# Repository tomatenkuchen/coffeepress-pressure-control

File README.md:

# La Pavoni Europiccola with embedded electronic pressure control
Pavoni Espresso Makers in their oldtimer form come with limited and inefficient steam pressure control (litterally steam all you can, and vent the surplus away). 
A power control via TRIAC and electronic pressure sensor can make a significant difference on power intake and startup time.

Attention! This design involves dealing with high voltages that can be dealy of lead to serious injury. Only qualified personel is allowed to assemble, test and use these schematics. There's no warranity or responsibility from my side, if things go wrong.
## documentation
all documentation is found in form of an [mdbook](https://rust-lang.github.io/mdBook/index.html).

## hardware
as this project is esp32 based, we need a pcb to mount the chip, the sensors and the power stage. the pcb design and component simulation was made with kicad 8.

## software
software is planned to be a rust embedded project.

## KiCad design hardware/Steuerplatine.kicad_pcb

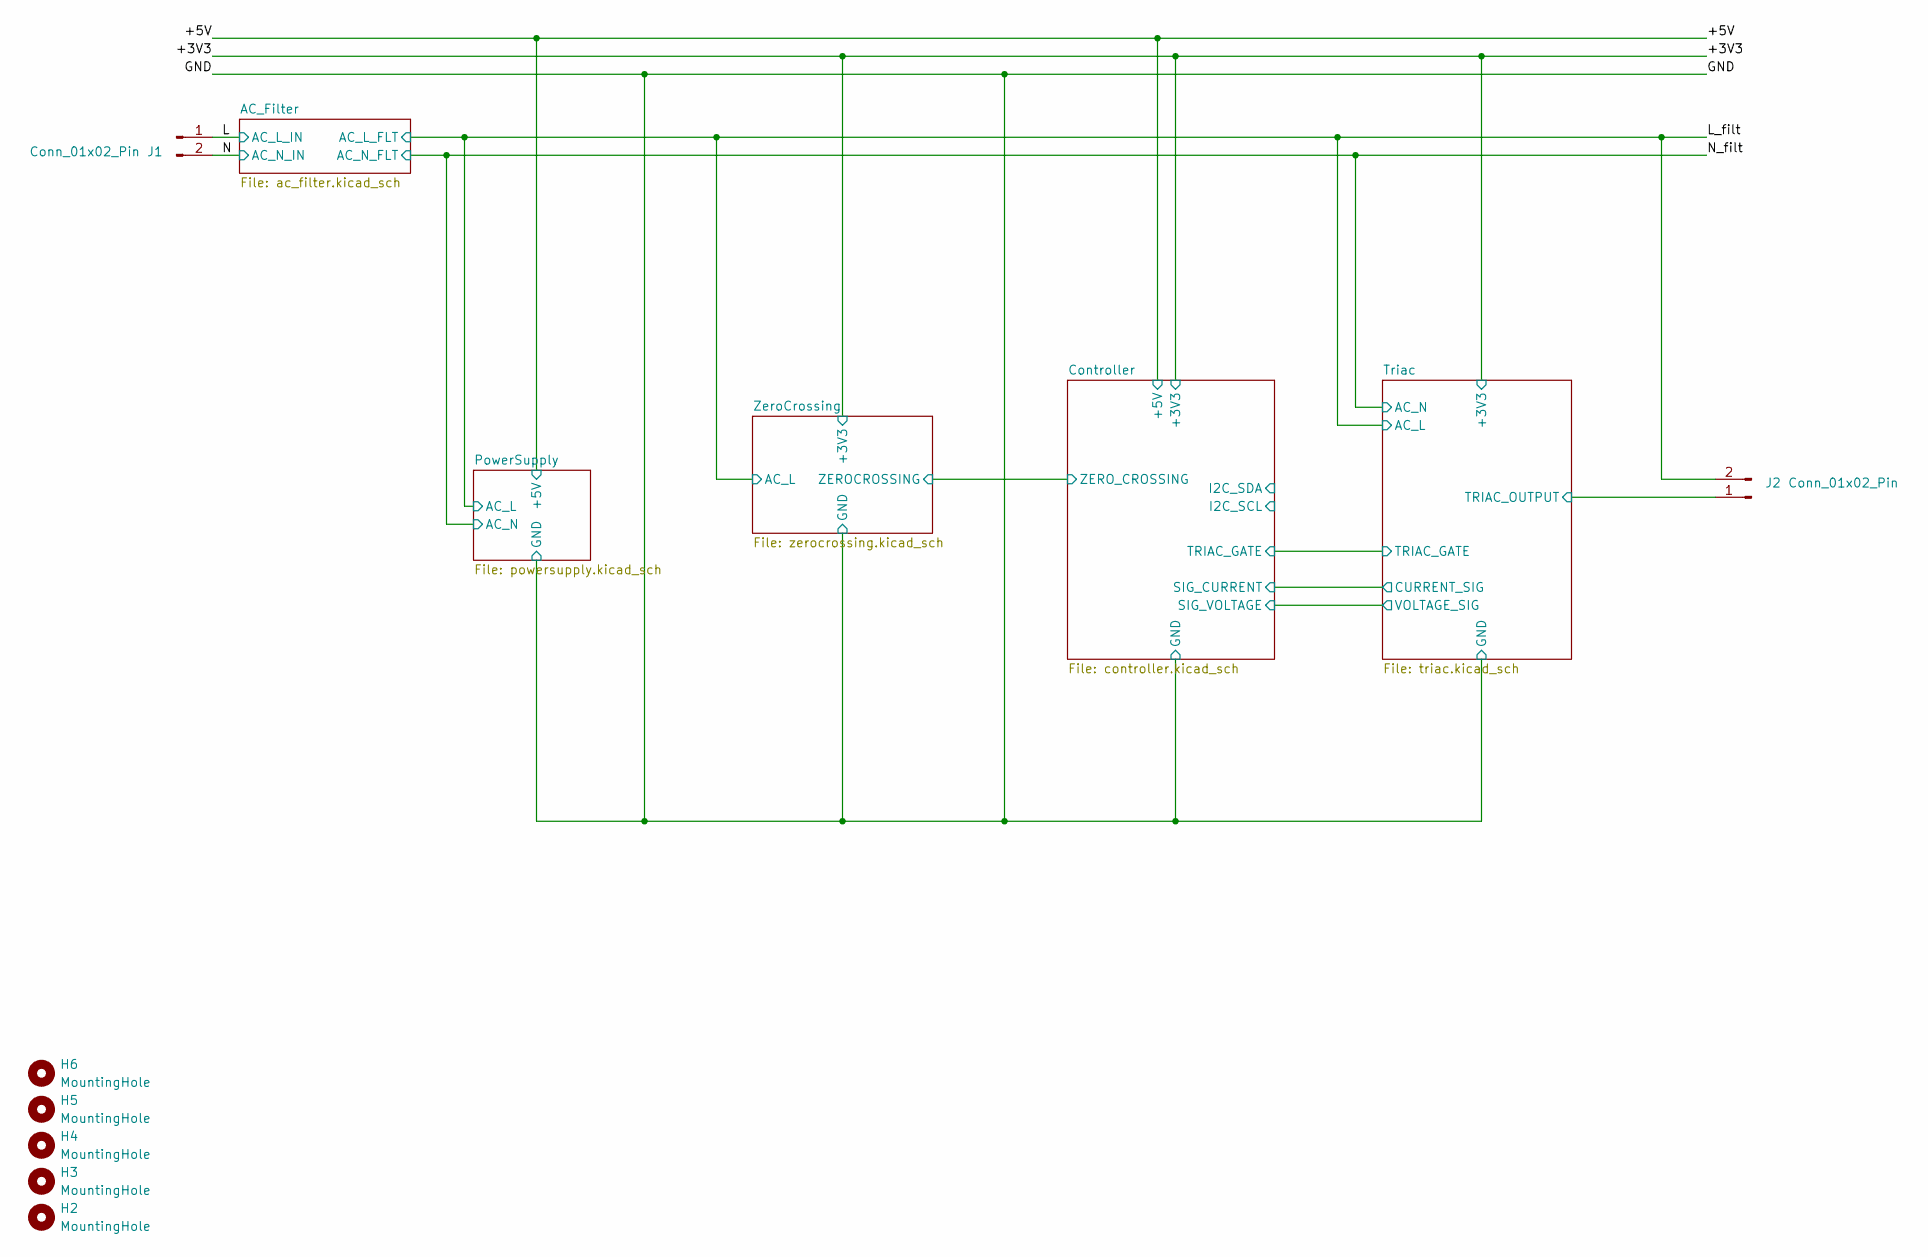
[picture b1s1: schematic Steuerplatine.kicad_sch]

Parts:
H2, H3, H4, H5, H6: MountingHole; MountingHole_3.5mm
J1, J2: Conn_01x02_Pin; PhoenixContact_MSTBA_2,5_2-G_1x02_P5.00mm_Horizontal

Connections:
/L: J1.1, J2.2; also elsewhere on the board
/N: J1.2; also elsewhere on the board
/Triac/TRIAC_OUTPUT: J2.1; also elsewhere on the board

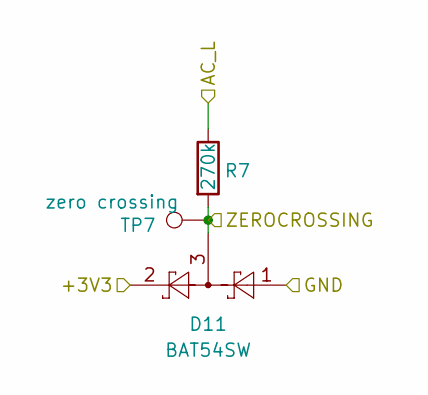
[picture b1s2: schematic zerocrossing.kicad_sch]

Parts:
D11: BAT54SW; SOT-23
R7: 270k; R_MELF_MMB-0207
TP7: zero crossing; TestPoint_Pad_D1.0mm

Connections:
/+3V3: D11.2; also elsewhere on the board
/Controller/ZERO_CROSSING: D11.3, R7.2, TP7.1; also elsewhere on the board
/GND: D11.1; also elsewhere on the board
/L: R7.1; also elsewhere on the board

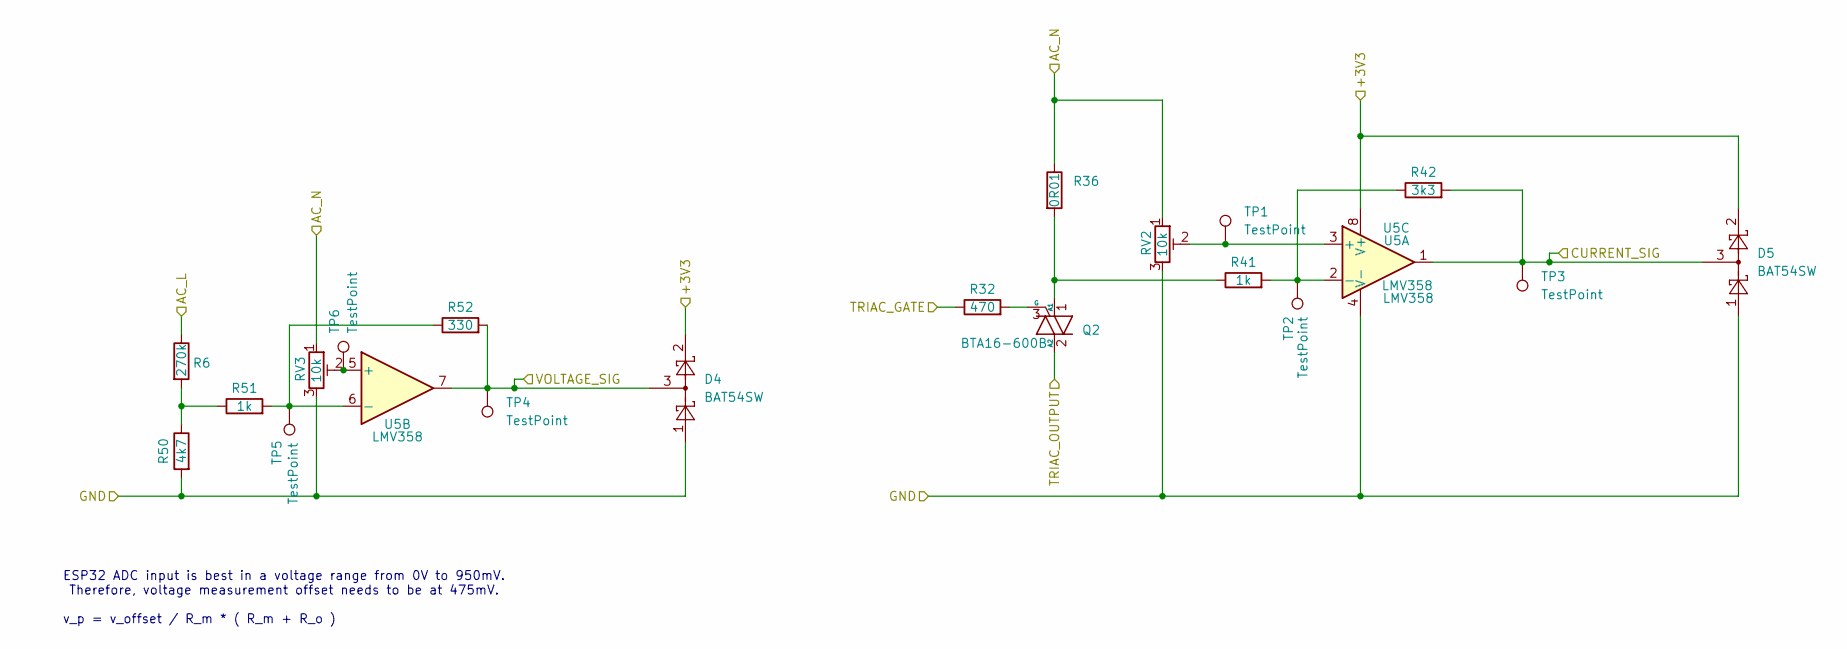
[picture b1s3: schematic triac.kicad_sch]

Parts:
D4, D5: BAT54SW; SOT-23
Q2: BTA16-600B; TO-220-3_Horizontal_TabDown
R6: 270k; R_MELF_MMB-0207
R32: 470; R_0603_1608Metric
R36: 0R01; R_2512_6332Metric
R41, R51: 1k; R_0603_1608Metric
R42: 3k3; R_0603_1608Metric
R50: 4k7; R_0603_1608Metric
R52: 330; R_0603_1608Metric
RV2, RV3: 10k; Potentiometer_Bourns_3299W_Vertical
TP1, TP2, TP3, TP4, TP5, TP6: TestPoint; TestPoint_Pad_D1.0mm
U5: LMV358; SOIC-8_3.9x4.9mm_P1.27mm

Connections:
/+3V3: D4.2, D5.2, U5.8 (V+); also elsewhere on the board
/Controller/SIG_CURRENT: D5.3, R42.2, TP3.1, U5.1; also elsewhere on the board
/Controller/SIG_VOLTAGE: D4.3, R52.2, TP4.1, U5.7; also elsewhere on the board
/Controller/TRIAC_GATE: R32.1; also elsewhere on the board
/GND: D4.1, D5.1, R50.2, RV2.3, RV3.3, U5.4 (V-); also elsewhere on the board
/L: R6.1; also elsewhere on the board
/N_filt: R36.1, RV2.1, RV3.1; also elsewhere on the board
/Triac/TRIAC_OUTPUT: Q2.2 (A2); also elsewhere on the board
unnamed: Q2.1 (A1), R36.2, R41.1
unnamed: Q2.3 (G), R32.2
unnamed: R6.2, R50.1, R51.1
unnamed: RV2.2, TP1.1, U5.3 (+)
unnamed: R41.2, R42.1, TP2.1, U5.2 (-)
unnamed: RV3.2, TP6.1, U5.5 (+)
unnamed: R51.2, R52.1, TP5.1, U5.6 (-)

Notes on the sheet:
ESP32 ADC input is best in a voltage range from 0V to 950mV. Therefore, voltage measurement offset needs to be at 475mV.
v_p = v_offset / R_m * ( R_m + R_o )

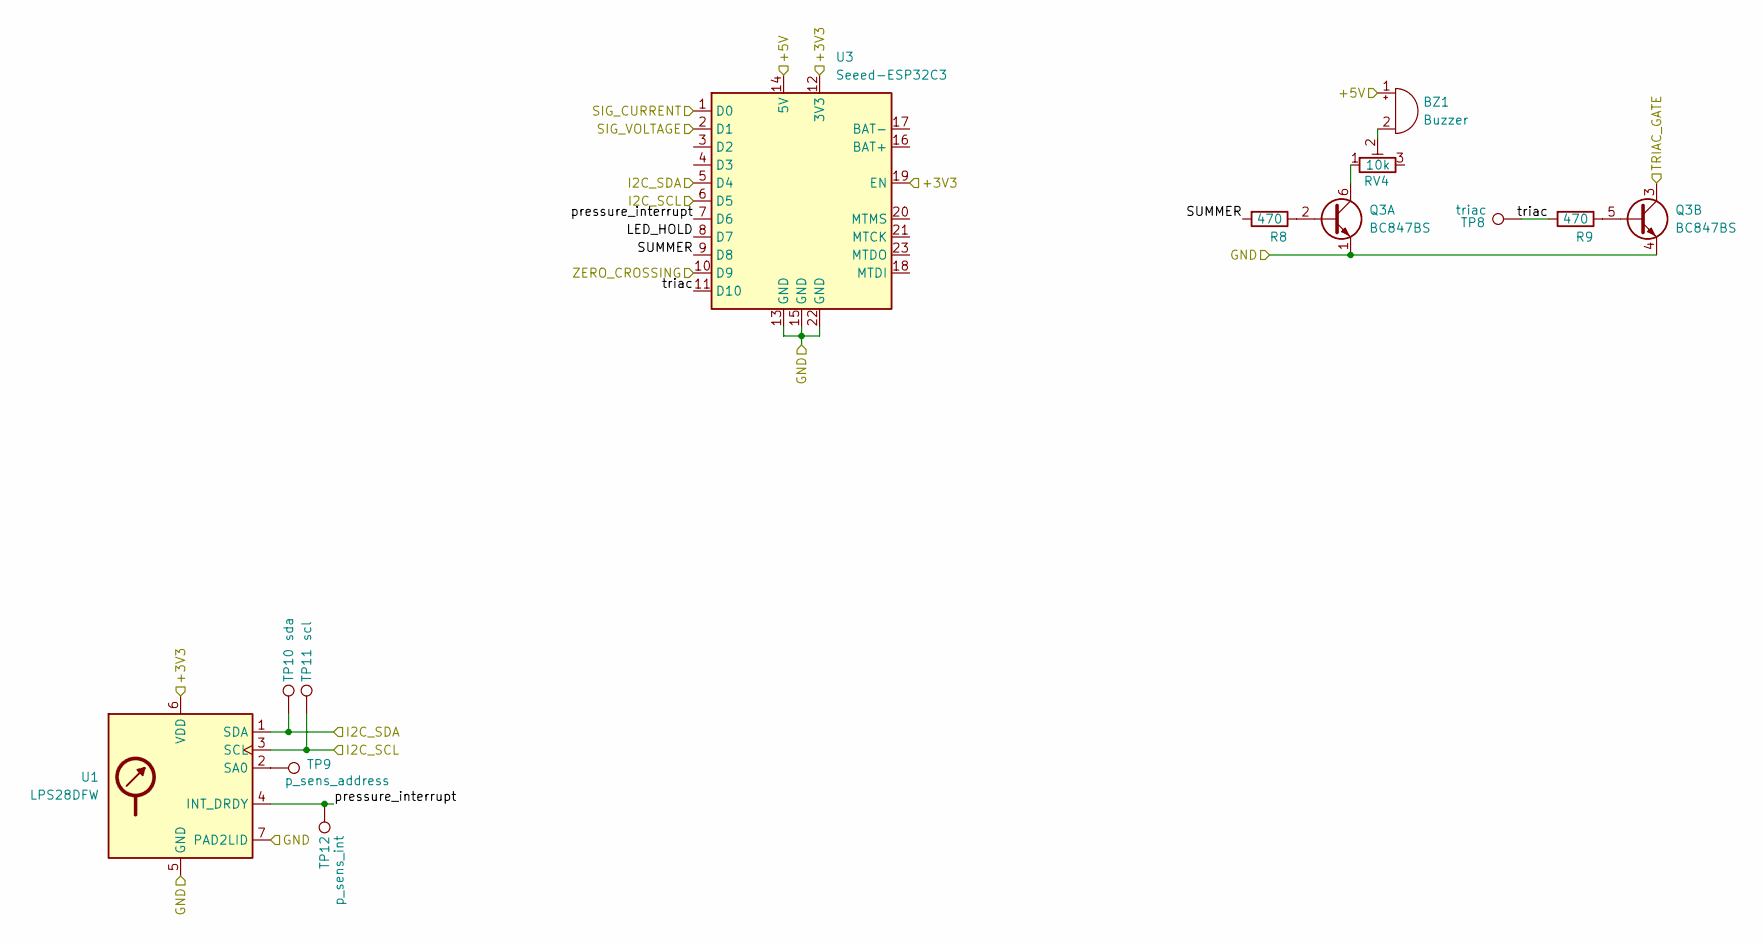
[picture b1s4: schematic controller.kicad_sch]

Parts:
BZ1: Buzzer; Buzzer_15x7.5RM7.6
Q3: BC847BS; SOT-363_SC-70-6
R8, R9: 470; R_0603_1608Metric
RV4: 10k; Potentiometer_Bourns_3299W_Vertical
TP8: triac; TestPoint_Pad_D1.0mm
TP9: p_sens_address; TestPoint_Pad_D1.0mm
TP10: sda; TestPoint_Pad_D1.0mm
TP11: scl; TestPoint_Pad_D1.0mm
TP12: p_sens_int; TestPoint_Pad_D1.0mm
U1: LPS28DFW; ST_LPS28DFW
U3: Seeed-ESP32C3; MCU_Seeed_ESP32C3

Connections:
/+3V3: U1.6 (VDD), U3.12 (3V3), U3.19 (EN); also elsewhere on the board
/+5V: BZ1.1 (-), U3.14 (5V); also elsewhere on the board
/Controller/I2C_SCL: TP11.1, U1.3 (SCL), U3.6 (D5)
/Controller/I2C_SDA: TP10.1, U1.1 (SDA), U3.5 (D4)
/Controller/LED_HOLD: U3.8 (D7)
/Controller/SIG_CURRENT: U3.1 (D0); also elsewhere on the board
/Controller/SIG_VOLTAGE: U3.2 (D1); also elsewhere on the board
/Controller/SUMMER: R8.2, U3.9 (D8)
/Controller/TRIAC_GATE: Q3.3 (C2); also elsewhere on the board
/Controller/ZERO_CROSSING: U3.10 (D9); also elsewhere on the board
/Controller/pressure_interrupt: TP12.1, U1.4 (INT_DRDY), U3.7 (D6)
/Controller/triac: R9.2, TP8.1, U3.11 (D10)
/GND: Q3.1 (E1), Q3.4 (E2), U1.5 (GND), U1.7 (PAD2LID), U3.13 (GND), U3.15 (GND), U3.22 (GND); also elsewhere on the board
unnamed: BZ1.2 (+), RV4.2
unnamed: Q3.2 (B1), R8.1
unnamed: Q3.6 (C1), RV4.1
unnamed: Q3.5 (B2), R9.1
unnamed: TP9.1, U1.2 (SA0)

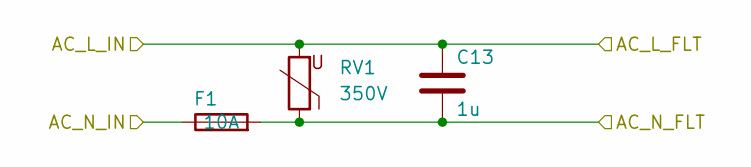
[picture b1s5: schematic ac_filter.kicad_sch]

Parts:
C13: 1u; C_Rect_L18.0mm_W8.0mm_P15.00mm_FKS3_FKP3
F1: 10A; Fuseholder_Clip-5x20mm_Schurter_CQM_Inline_P20.60x5.00mm_D1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
RV1: 350V; RV_Disc_D12mm_W4.2mm_P7.5mm

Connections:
/L: C13.1, RV1.2; also elsewhere on the board
/N: F1.1; also elsewhere on the board
/N_filt: C13.2, F1.2, RV1.1; also elsewhere on the board

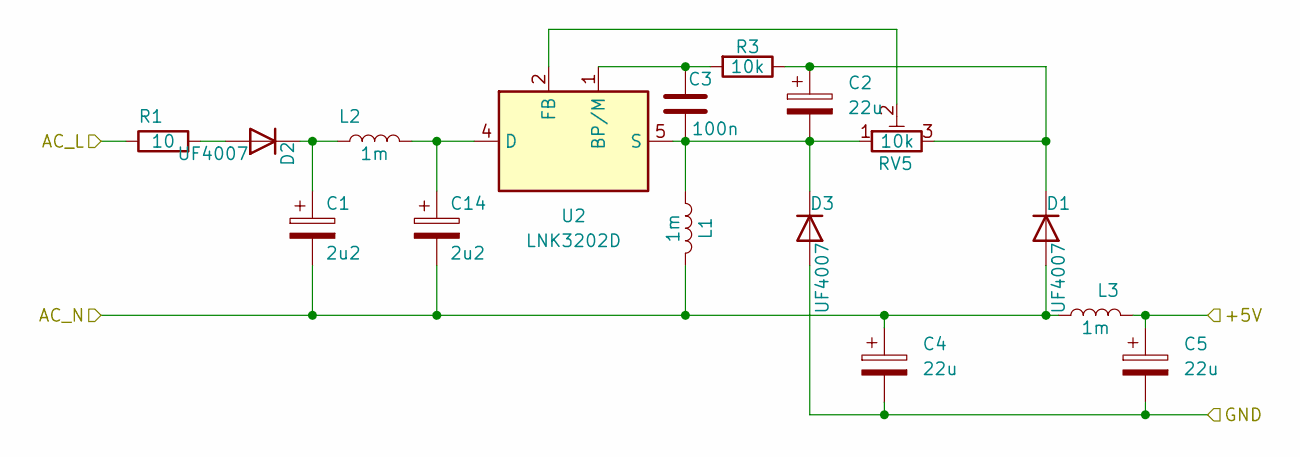
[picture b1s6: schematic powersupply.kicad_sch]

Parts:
C1, C14: 2u2; CP_Elec_8x10
C2, C4, C5: 22u; CP_Elec_6.3x3
C3: 100n; C_0603_1608Metric
D1, D2, D3: UF4007; D_SMB
L1, L2, L3: 1m; L_Wuerth_WE-XHMI-8080
R1: 10; R_2816_7142Metric
R3: 10k; R_0603_1608Metric
RV5: 10k; Potentiometer_Bourns_3299W_Vertical
U2: LNK3202D; PowerIntegrations_SO-8C

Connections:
/+5V: C5.1, L3.2; also elsewhere on the board
/GND: C4.2, C5.2, D3.2 (A); also elsewhere on the board
/L: R1.1; also elsewhere on the board
/N_filt: C1.2, C4.1, C14.2, D1.2 (A), L1.2, L3.1; also elsewhere on the board
unnamed: C2.1, D1.1 (K), R3.1, RV5.3
unnamed: D2.2 (A), R1.2
unnamed: C1.1, D2.1 (K), L2.1
unnamed: C2.2, C3.1, D3.1 (K), L1.1, RV5.1, U2.5 (S), U2.6 (S), U2.7 (S), U2.8 (S)
unnamed: C3.2, R3.2, U2.1 (BP/M)
unnamed: C14.1, L2.2, U2.4 (D)
unnamed: RV5.2, U2.2 (FB)

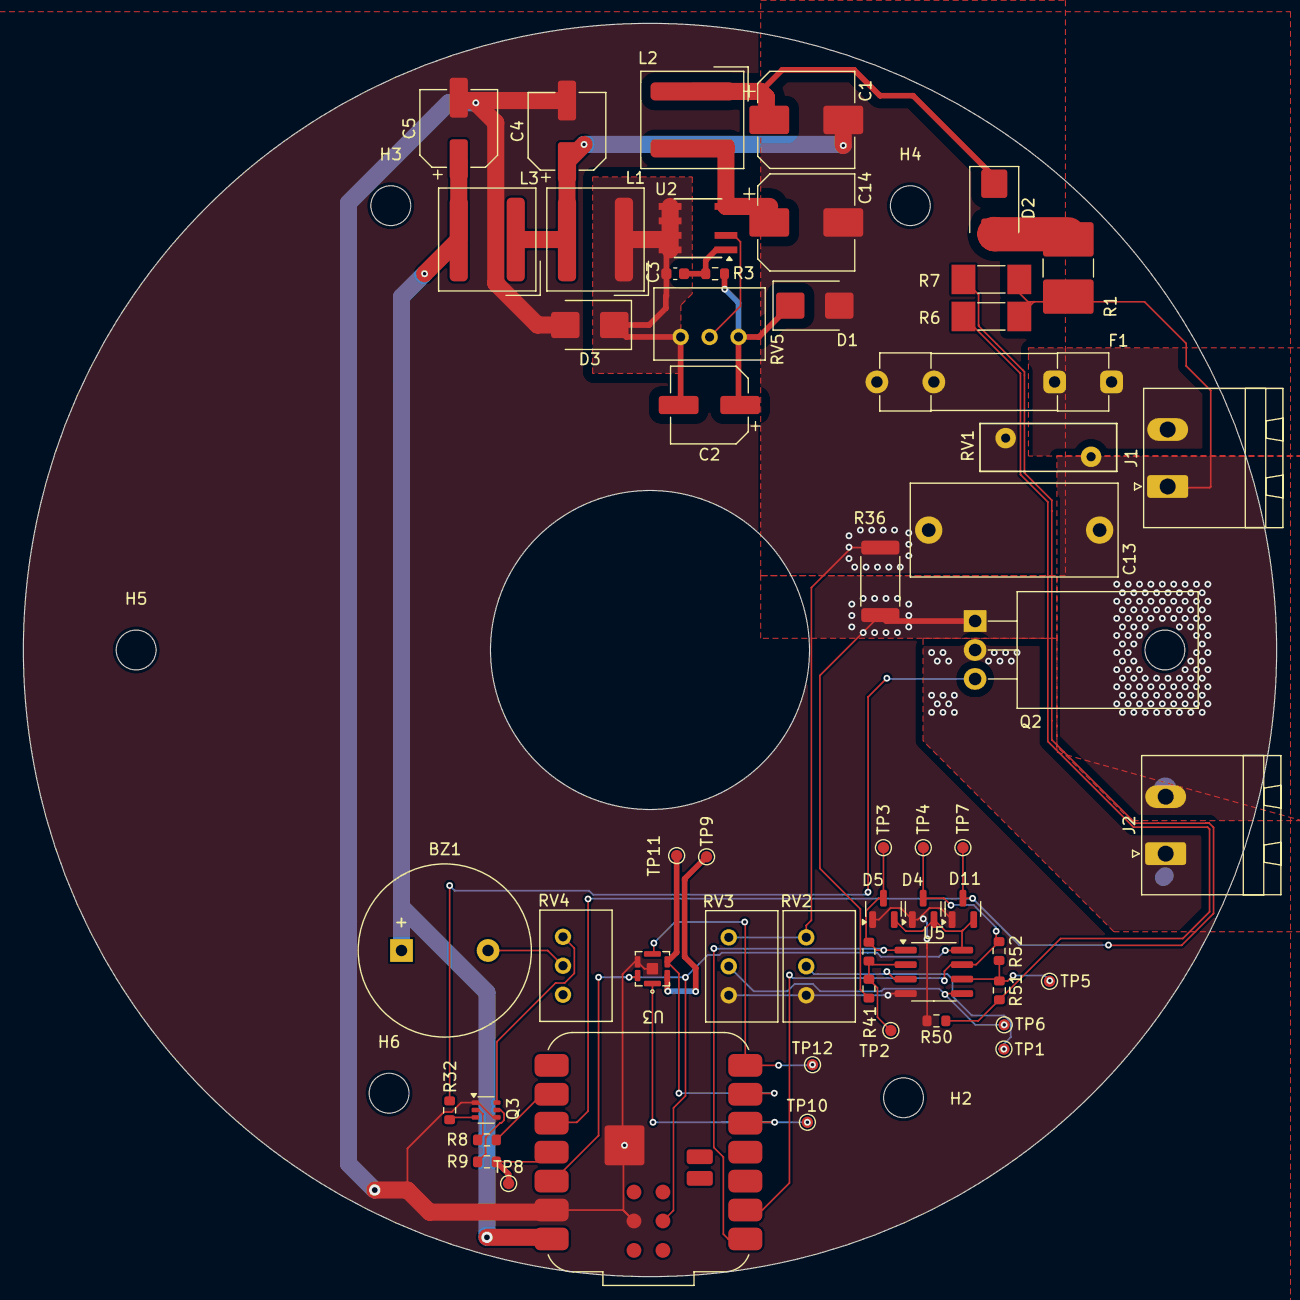
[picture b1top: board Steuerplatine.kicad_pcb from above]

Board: 2 copper layers, 110.0 x 110.0 mm, 61 parts (0 on the bottom side), 35 nets.

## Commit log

2024-03-08 root
2024-03-20 done routing
2024-03-23 added pressure sensor
2024-03-29 bugfix: triac output needs to confront L potential
2024-03-30 added some zones
2024-03-31 added some datasheets
2024-03-31 ignore bom
2024-03-31 some more rules and routings
2024-03-31 changed capacitors to smd
2024-03-31 changed diodes footprint
2024-03-31 added gnd layer
2024-04-01 restructured copper planes
2024-04-01 changed some parts to stuff you can actually order
2024-04-01 added testpoints. adjusted opamps for correct measurement. replaced hard resistors with potentiometer trimmers if necessary
2024-04-01 updated readme with danger sign
2024-04-04 moved rust project to src folder. updated dependencies to maintained crates
2024-04-07 moved softwrae from rust subfolder to software folder. removed duplicate LICENSE files
2024-04-07 removed old rust folder
2024-05-07 changed opamp for a rail-to-rail device. bugfix: got the right package for phoenix mstba outlets. beauty: rearranged some test points for better visibility. bugfix: added bypass diodes to analog outp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
2024-05-12 got a first running software for adc access
2024-05-18 added voltage adc input
2024-05-18 added i2c
2024-05-20 added identity request on i2c
2024-07-07 changed i2c request to sensor request
2024-07-13 updated embedded hal crate
2024-07-15 updated pressure sensor driver to a nostd friendly version.
    updated main to esp-hal 0.18.0 standart
2024-07-16 updated firmware versions
2024-07-16 updated to more modern esp32 template. added wifi modules
2024-07-16 removed la pavoni from title
